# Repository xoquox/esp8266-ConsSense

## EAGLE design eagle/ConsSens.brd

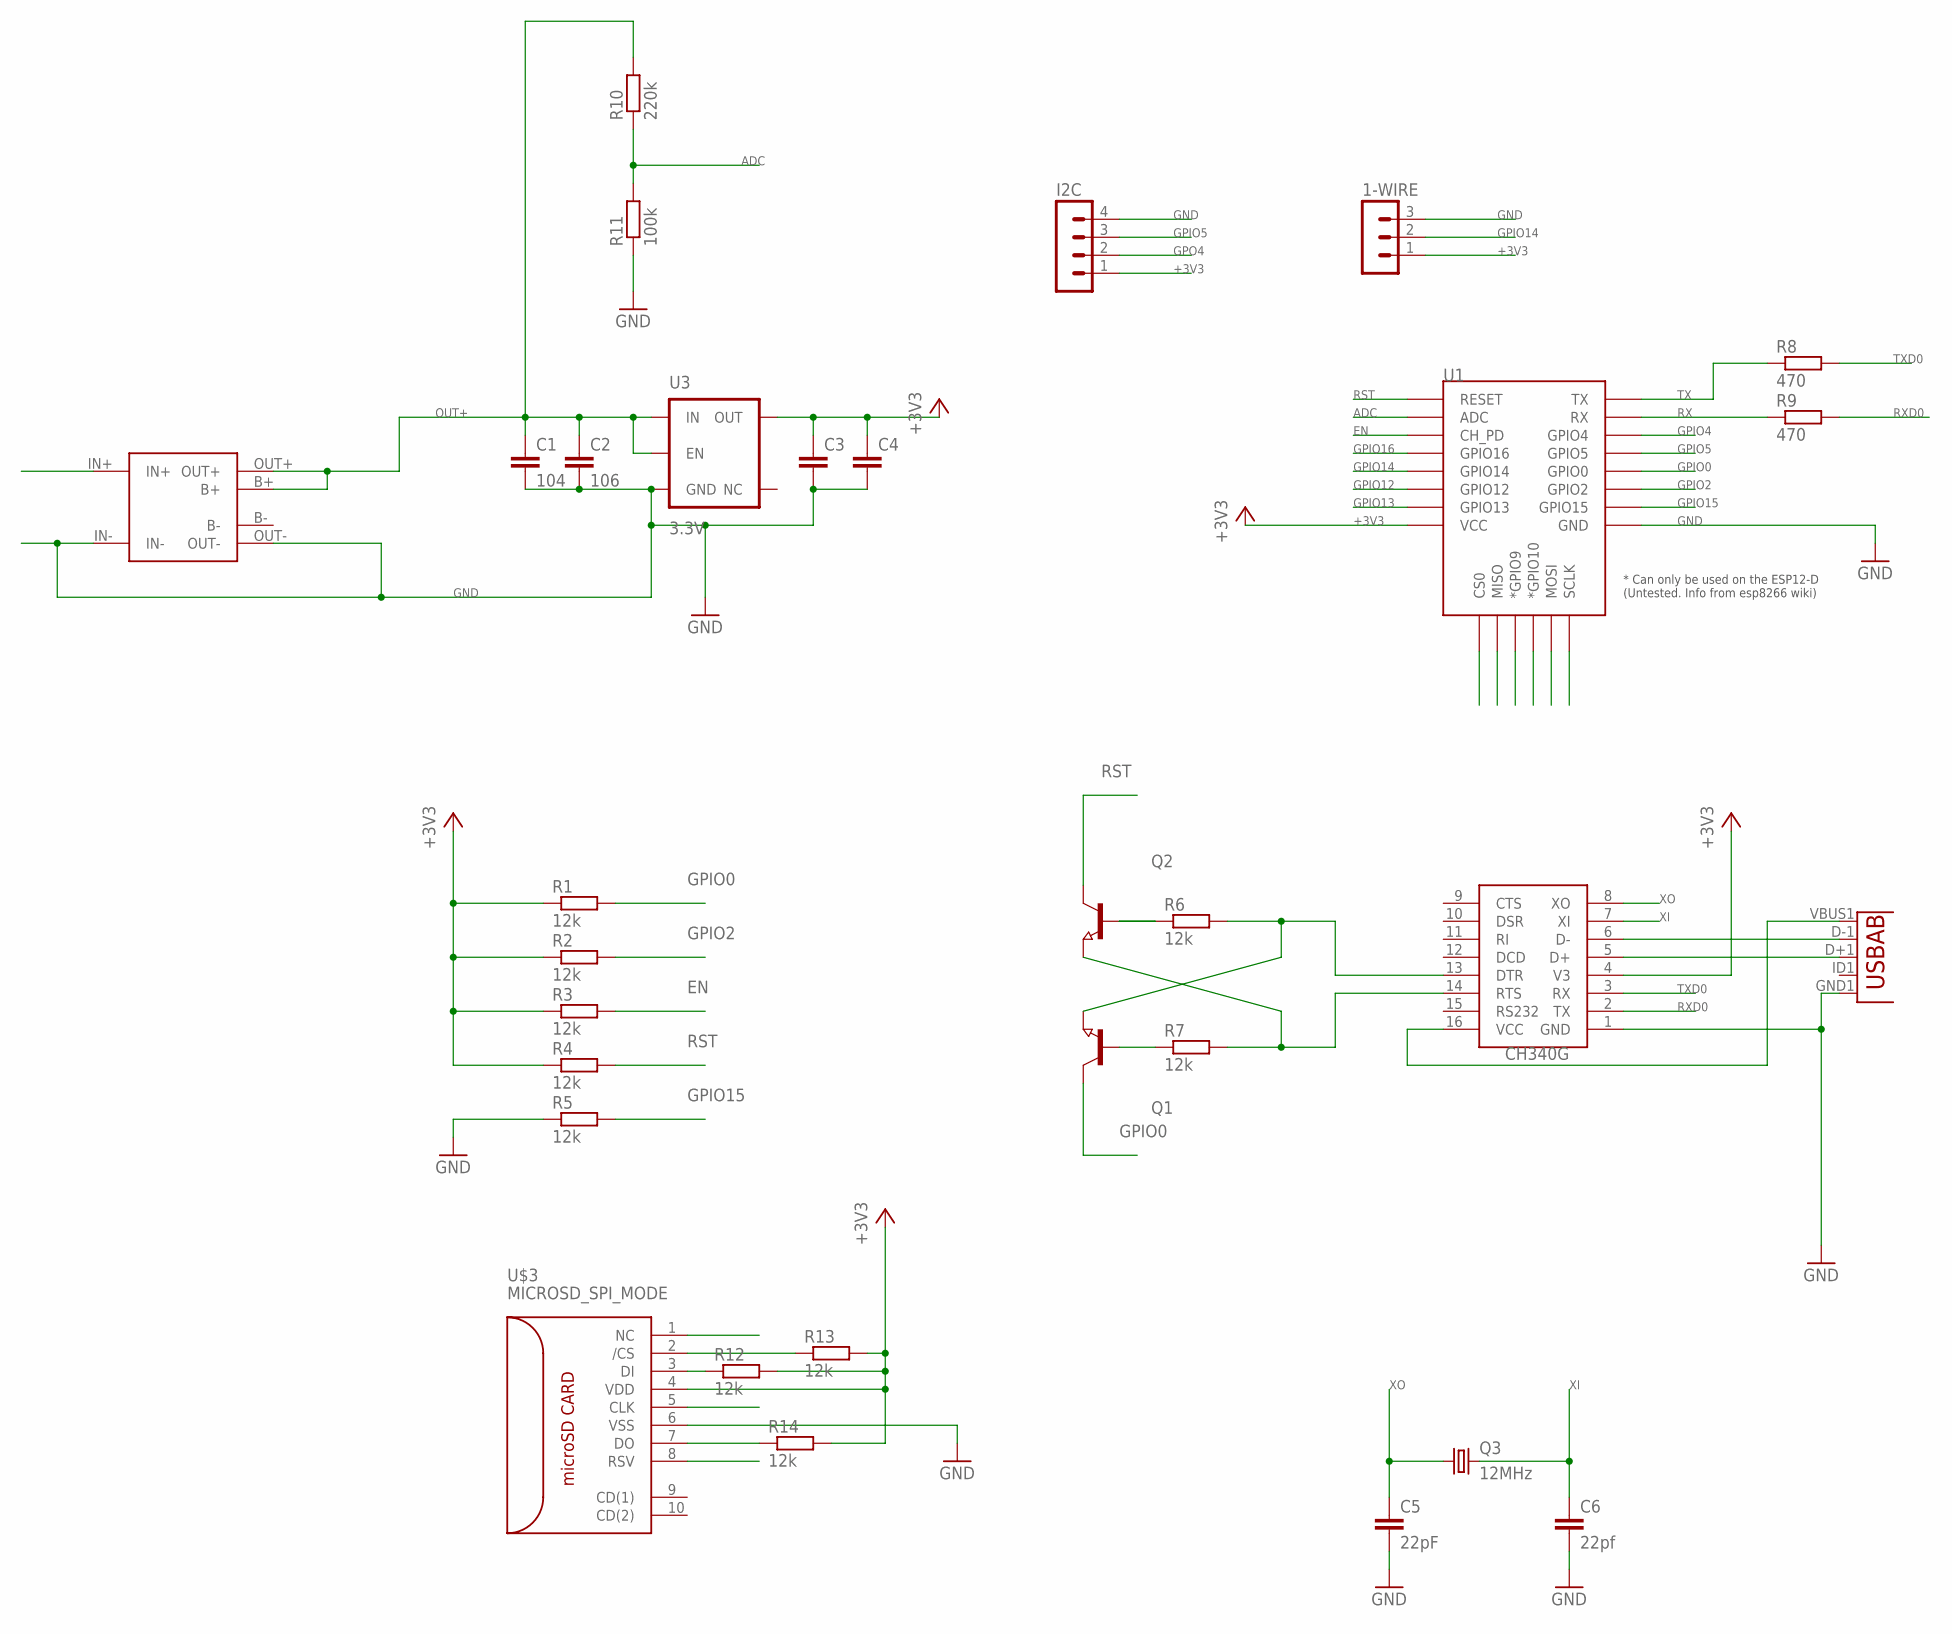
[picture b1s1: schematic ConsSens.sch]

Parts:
1-WIRE: MA03-1
C1: 104; C0805
C2: 106; C0805
C3, C4: C-EUC0805; C0805
C5: 22pF; C0805
C6: 22pf; C0805
I2C: MA04-1
MICROUSB: USB""; USB-MICRO-SMD
Q1, Q2: NPN-TRANSISTOR_SOT23; SOT23
Q3: 12MHz; CRYSTAL-SMD-5X3
R1, R2, R3, R4, R5, R6, R7, R12, R13, R14: 12k; R0603
R8, R9: 470; R0603
R10: 220k; R0603
R11: 100k; R0603
U1: ESP12ESMD; ESP12E-SMD
U3: 3.3V; SOT23-5
U$1: CH340G; SOIC16
U$3: MICROSD_SPI_MODE; MICRO_SD_CONNECTOR
U$4: TP4056-MODULE; TP4056-LITHIUM-PROTECTED-MODULE

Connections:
+3V3: 1-WIRE.1, C3.1, C4.1, I2C.1, R1.1, R2.1, R3.1, R4.1, U1.VCC, U3.5 (OUT), U$1.4 (V3)
ADC: R10.1, R11.2, U1.ADC
B-: U$4.B-
EN: R3.2, U1.CH_PD
GND: 1-WIRE.3, C1.2, C2.2, C3.2, C4.2, C5.2, C6.2, I2C.4, MICROUSB.GND1 (GND), R5.1, R11.1, R12.2, R13.2, R14.2, U1.GND, U3.2 (GND), U$1.1 (GND), U$3.4 (VDD), U$3.6 (VSS), U$4.IN-, U$4.OUT-
GPIO0: Q1.3 (C), R1.2, U1.GPIO0
GPIO2: R2.2, U1.GPIO2
GPIO4: U1.GPIO4
GPIO5: I2C.3, U1.GPIO5
GPIO12: R14.1, U1.GPIO12, U$3.7 (DO)
GPIO13: R12.1, U1.GPIO13, U$3.3 (DI)
GPIO14: 1-WIRE.2, U1.GPIO14, U$3.5 (CLK)
GPIO15: R5.2, R13.1, U1.GPIO15, U$3.2 (/CS)
GPIO16: U1.GPIO16
GPO4: I2C.2
unnamed: Q1.1 (B), R7.1
unnamed: Q2.1 (B), R6.1
unnamed: Q2.2 (E), R7.2, U$1.14 (RTS)
unnamed: Q1.2 (E), R6.2, U$1.13 (DTR)
unnamed: MICROUSB.D-1 (D-), U$1.6 (D-)
unnamed: MICROUSB.D+1 (D+), U$1.5 (D+)
OUT+: C1.1, C2.1, R10.2, U3.1 (IN), U3.3 (EN), U$4.B+, U$4.OUT+
RST: Q2.3 (C), R4.2, U1.RESET
RX: R9.1, U1.RXD0 (RX)
RXD0: R9.2, U$1.2 (TX)
TX: R8.1, U1.TXD0 (TX)
TXD0: R8.2, U$1.3 (RX)
USB5V: MICROUSB.VBUS1 (VBUS), U$1.16 (VCC), U$4.IN+
XI: C6.1, Q3.3 (2), U$1.7 (XI)
XO: C5.1, Q3.1, U$1.8 (XO)

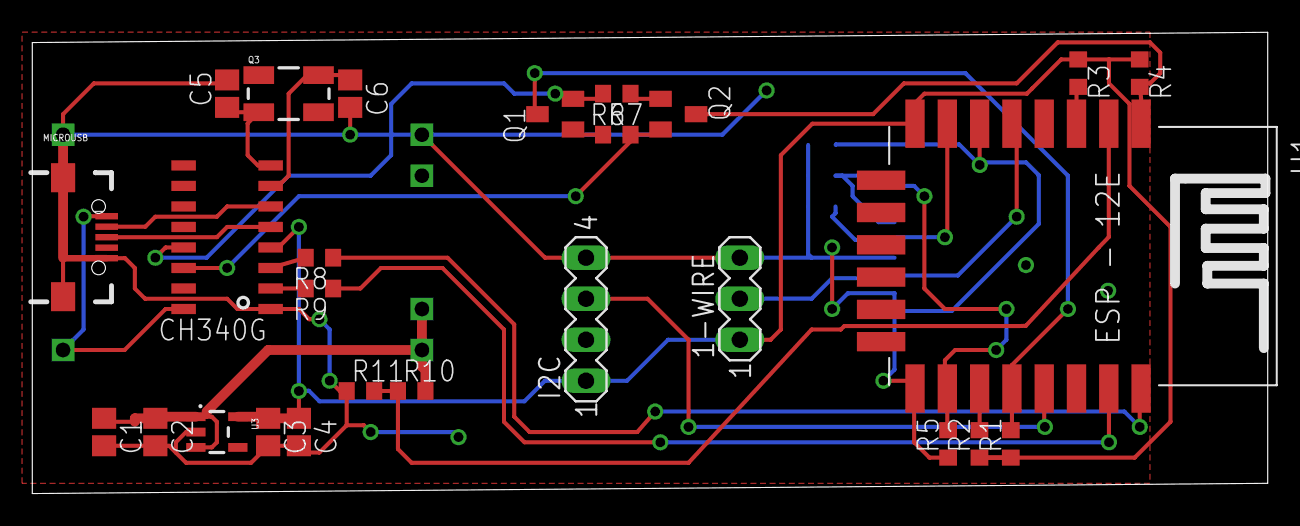
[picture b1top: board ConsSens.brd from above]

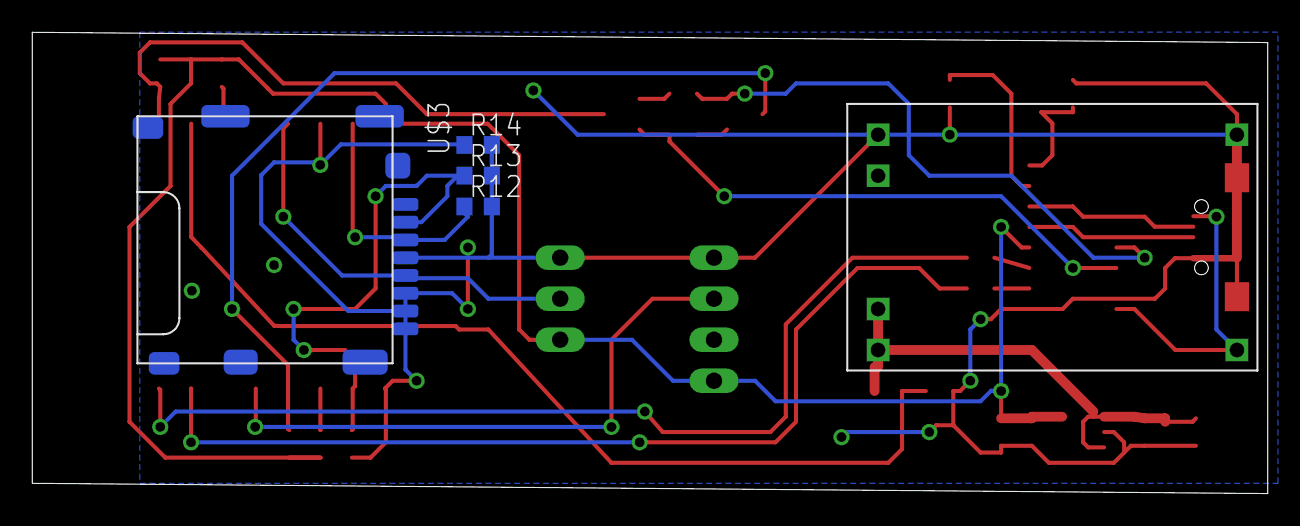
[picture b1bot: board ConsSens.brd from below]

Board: 2 copper layers, 76.5 x 28.6 mm, 31 parts (5 on the bottom side), 26 nets.

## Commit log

2016-05-24 eagle files added
2016-05-26 some new parts added to the layout, usb-serial eagle lib added
2016-05-27 more layout added, also new eagle libs, and datasheets
2016-05-29 first routing
2016-10-11 Fixed some design errors in board layout
2016-10-12 fixed wrong size from LiPo Charge Modul
2016-10-18 New Micro-USB Connector

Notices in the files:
parts and their libraries:
SparkFun-PowerIC: Licensing: Creative Commons ShareAlike 4.0 International - https://creativecommons.org/licenses/by-sa/4.0
